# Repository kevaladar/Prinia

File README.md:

# Prinia
Prinia is a 30-keys split keyboard base on Berylline in Hummingbird family.
to do prinia
1. unibody:
maybe change physical layout little bit
forgot to route r4
silkscreen smaller
change hole to 3.2mm (the hole 2.2mm is just for the srcew, not fit m2 standoff)
change switch footprint to unreversible (no need reversible in this.)
it the rev 0.2

2. for split
- change silkscreen, my cicada look like a fly
- change orientation (angle) of hatched filled zone for aesthetic (rotate keyboard full 8 degree) 
- delete jlcjlcjlc, they not gonna use it for order number

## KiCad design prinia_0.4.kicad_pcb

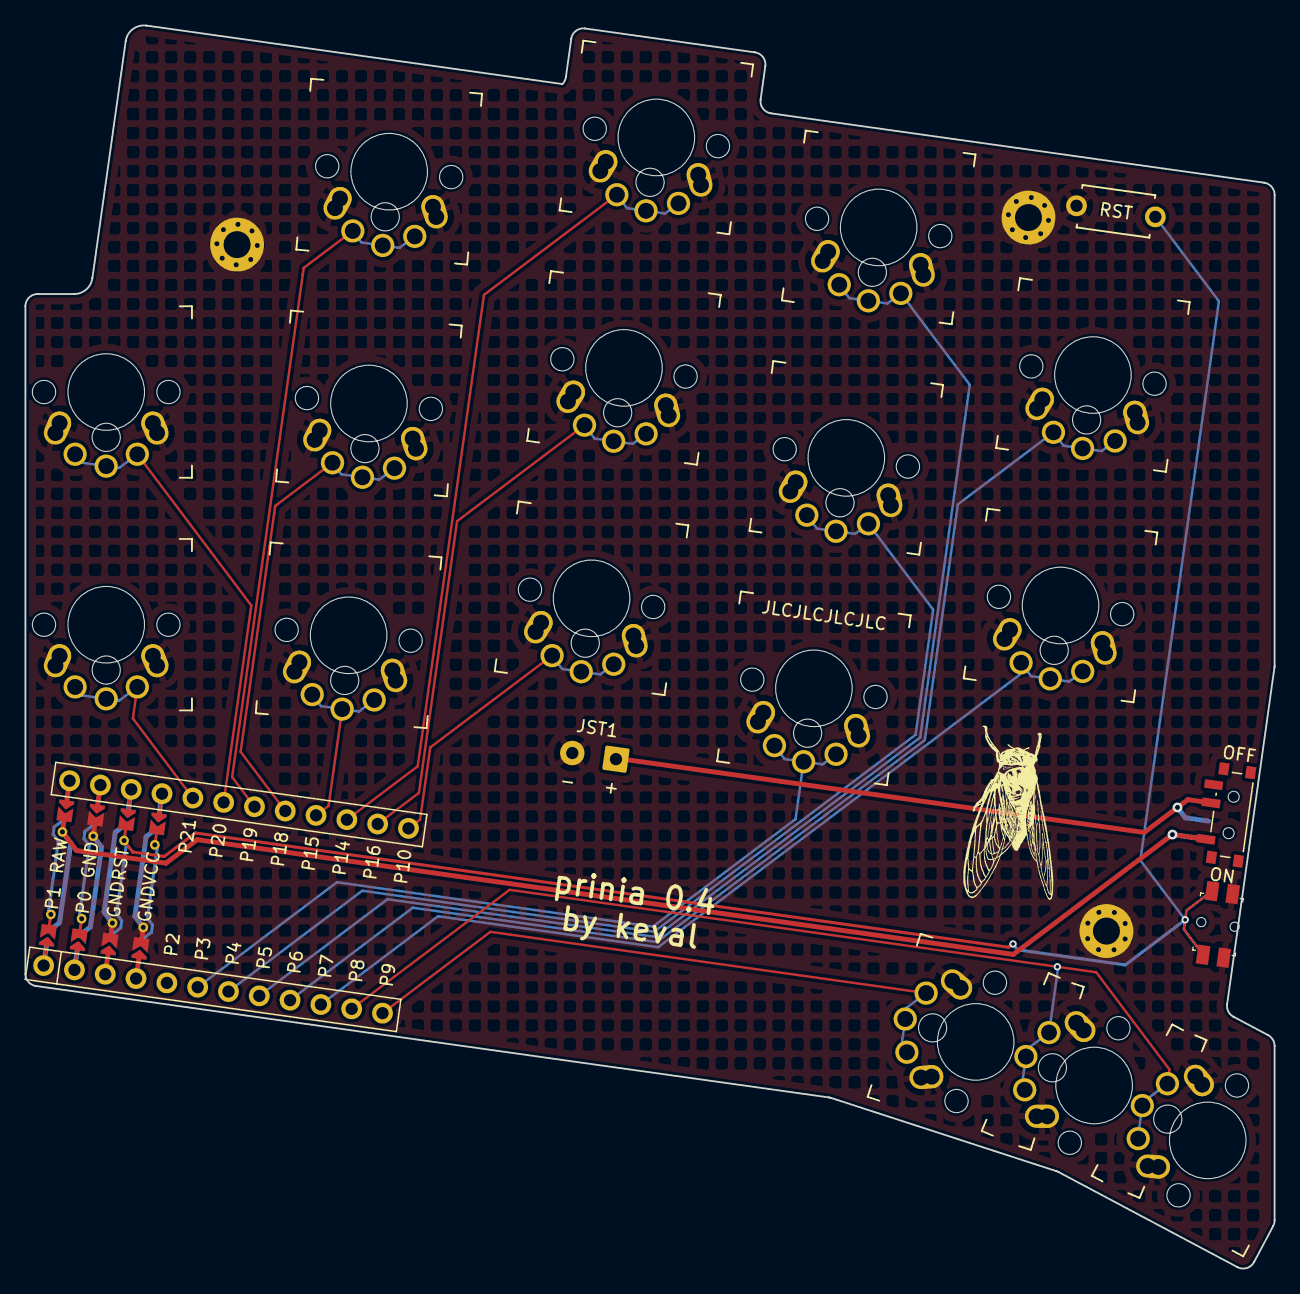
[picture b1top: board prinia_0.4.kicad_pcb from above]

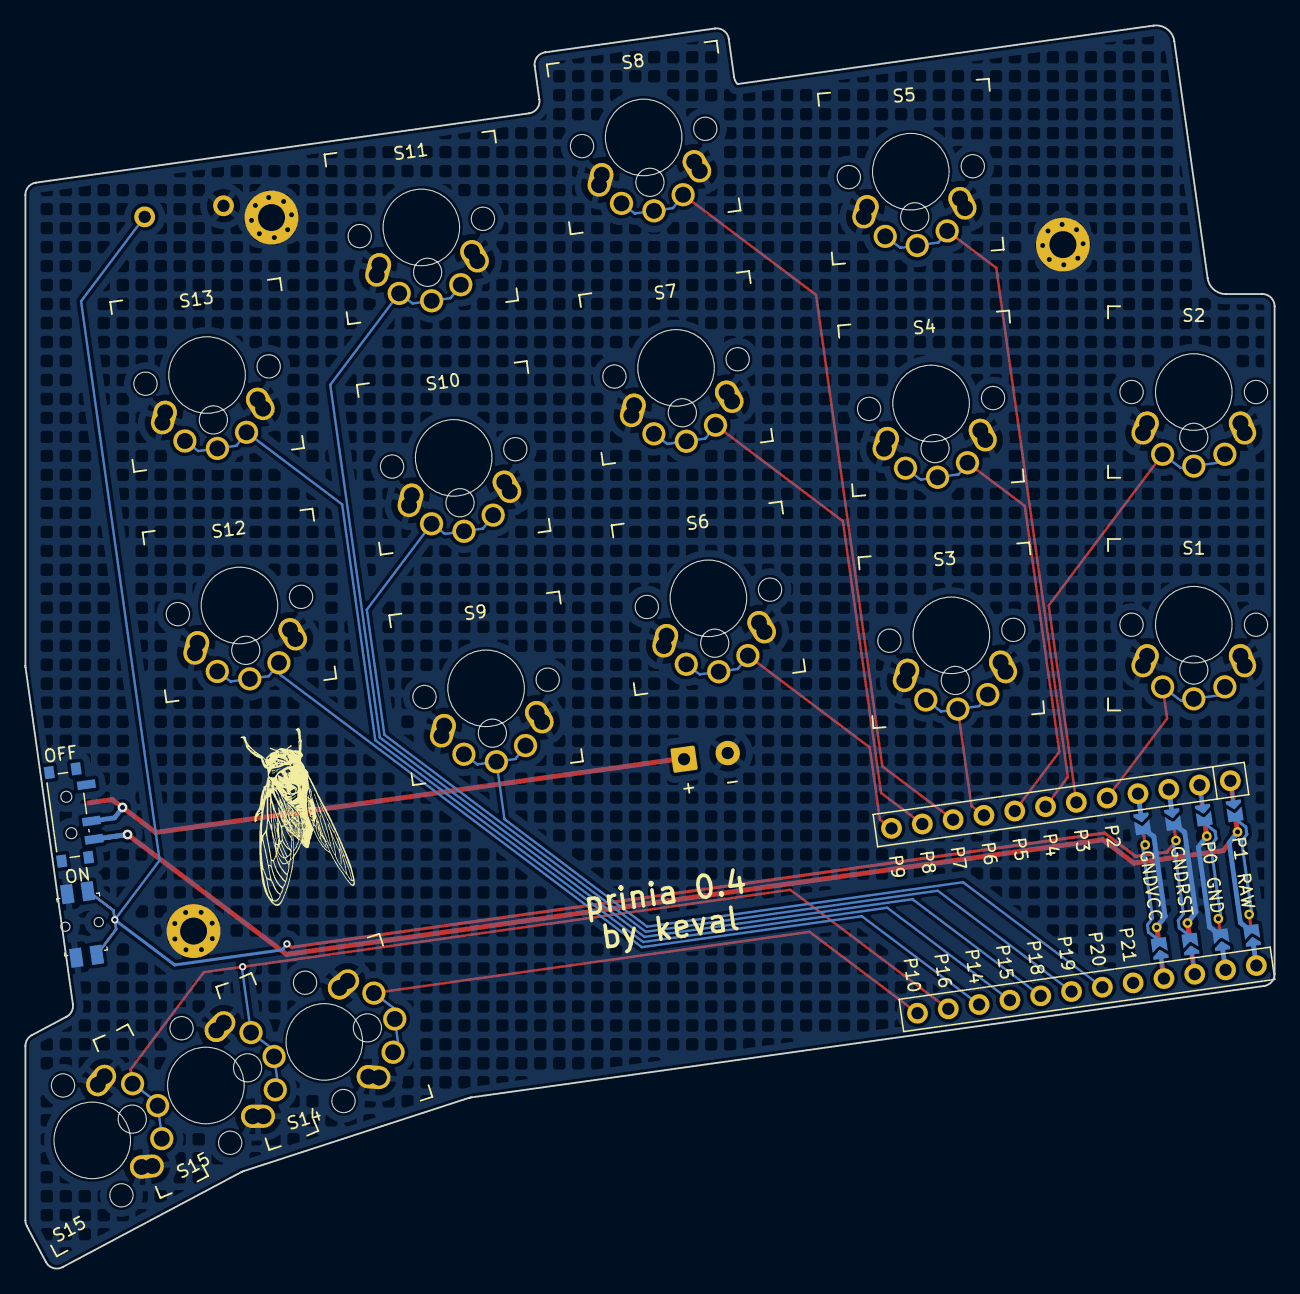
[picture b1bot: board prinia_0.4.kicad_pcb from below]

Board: 2 copper layers, 102.0 x 101.5 mm, 24 parts (16 on the bottom side), 19 nets.

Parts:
H1, H2, H3: MountingHole_2.2mm_M2_Pad_Via
JST1: Battery_Connector_Small
MCU1: mcu_supermini_nrf52840
PWR1: power_switch_smd_side
RST1: reset_switch_tht_top
RST_S1: reset_switch_smd_side
S1, S2, S3, S4, S5, S6, S7, S8, S9, S10, S11, S12, S13, S14, S15, S16: SW_MX_MXLP_reversible

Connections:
BAT_P: JST1.1, PWR1.2
GND: H1.1, H2.1, H3.1, JST1.2, MCU1.102, MCU1.121, MCU1.122, RST1.2, RST_S1.1, RST_S1.3, S1.1, S2.1, S3.1, S4.1, S5.1, S6.1, S7.1, S8.1, S9.1, S10.1, S11.1, S12.1, S13.1, S14.1, S15.1, S16.1
P3: MCU1.19, S9.2
P4: MCU1.18, S10.2
P5: MCU1.17, S11.2
P6: MCU1.16, S13.2
P7: MCU1.15, S12.2
P8: MCU1.14, S15.2, S16.2
P9: MCU1.13, S14.2
P10: MCU1.12, S6.2
P14: MCU1.10, S8.2
P15: MCU1.9, S3.2
P16: MCU1.11, S7.2
P18: MCU1.8, S4.2
P19: MCU1.7, S5.2
P20: MCU1.6, S2.2
P21: MCU1.5, S1.2
RAW: MCU1.101, PWR1.1, PWR1.3
RST: MCU1.103, RST1.1, RST_S1.2, RST_S1.4

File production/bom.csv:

Designator,Footprint,Quantity,Value,LCSC Part #
PWR1,power_switch_smd_side,1,,
RST1,reset_switch_tht_top,1,,
RST_S1,reset_switch_smd_side,1,,
"S1, S10, S11, S12, S13, S14, S15, S16, S2, S3, S4, S5, S6, S7, S8, S9",SW_MX_MXLP_reversible,16,,
